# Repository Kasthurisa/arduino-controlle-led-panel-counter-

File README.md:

# arduino-controlle-led-panel-counter-
this project explains how to build arduino controlled led panel counter.  you have to use 16*32 led panel and arduino. here i just used atmega 328p microcontroler.

here is the pin connection for led pannel 

 nOE(D9) |1     2| A(D6)
 Gnd     |3     4| B(D7)
 Gnd     |5     6| C
 Gnd     |6     8| CLK(D13)
 Gnd     |7    10| SCLK(D8)
 Gnd     |11   12| R(D11)
 Gnd     |13   14| G
 Gnd     |15   16| D

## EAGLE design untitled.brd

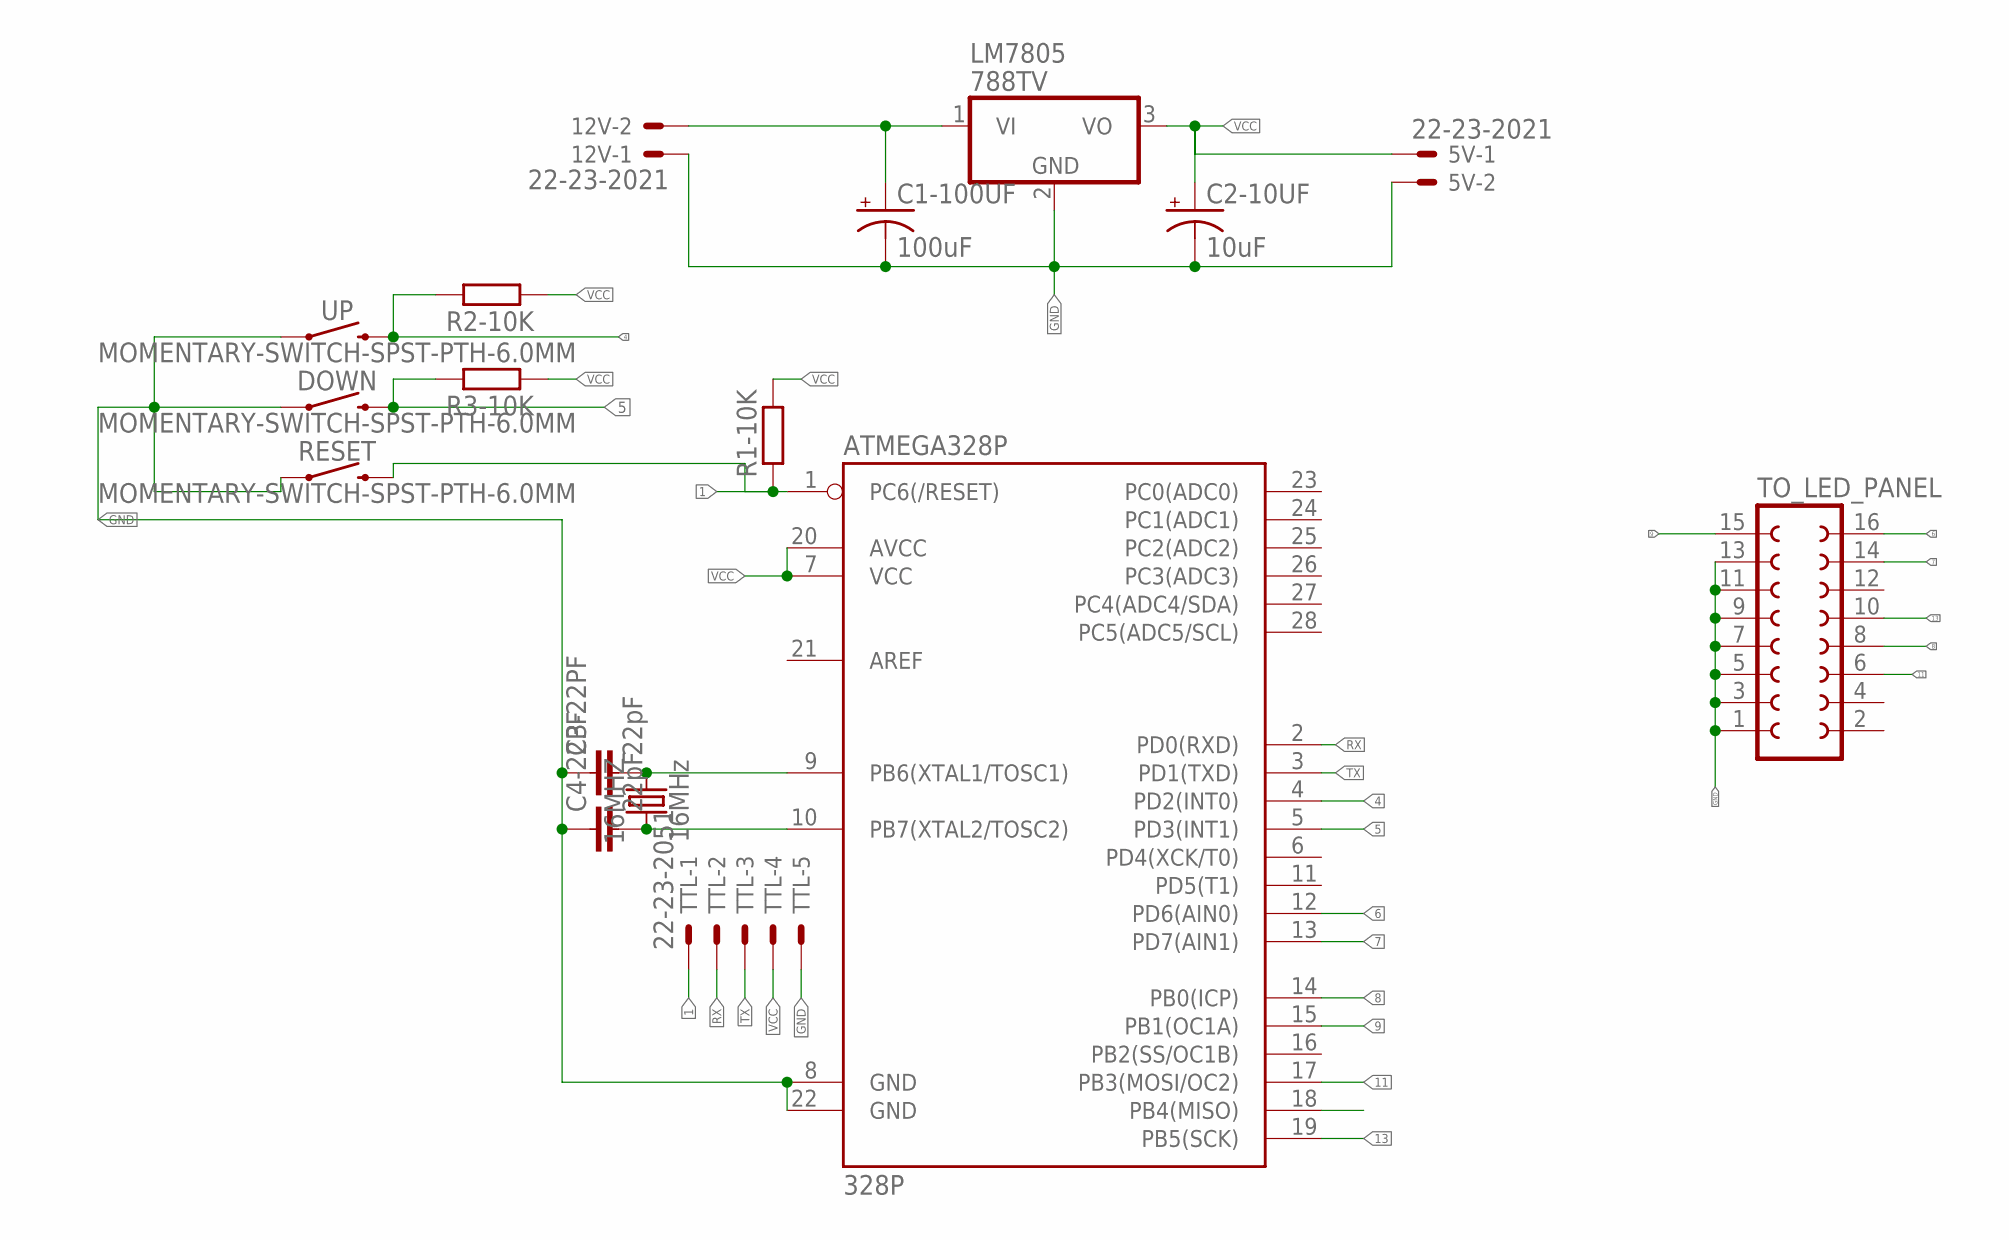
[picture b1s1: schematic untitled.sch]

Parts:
5V, 12V: 22-23-2021
16MHZ: 16MHz; HC49US
ATMEGA328P: 328P; DIP28
C1-100UF: 100uF; CPOL-RADIAL-2.5MM-6.5MM
C2-10UF: 10uF; CPOL-RADIAL-2.5MM-5MM
C3-22PF, C4-22PF: 22pF; CAP-PTH-2.54
DOWN: MOMENTARY-SWITCH-SPST-PTH-6.0MM; TACTILE_SWITCH_PTH_6.0MM
LM7805: 788TV; TO220V
R1-10K, R2-10K, R3-10K: R-EU_0207/10; 0207/10
RESET: MOMENTARY-SWITCH-SPST-PTH-6.0MM; TACTILE_SWITCH_PTH_6.0MM
TO_LED_PANEL: FE08-2
TTL: 22-23-2051
UP: MOMENTARY-SWITCH-SPST-PTH-6.0MM; TACTILE_SWITCH_PTH_6.0MM

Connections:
1: ATMEGA328P.1 (PC6(/RESET)), R1-10K.1, RESET.3 (2), TTL.1
4: ATMEGA328P.4 (PD2(INT0)), R2-10K.2, UP.3 (2)
5: ATMEGA328P.5 (PD3(INT1)), DOWN.3 (2), R3-10K.2
6: ATMEGA328P.12 (PD6(AIN0)), TO_LED_PANEL.16
7: ATMEGA328P.13 (PD7(AIN1)), TO_LED_PANEL.14
8: ATMEGA328P.14 (PB0(ICP)), TO_LED_PANEL.8
9: ATMEGA328P.15 (PB1(OC1A)), TO_LED_PANEL.15
11: ATMEGA328P.17 (PB3(MOSI/OC2)), TO_LED_PANEL.6
13: ATMEGA328P.19 (PB5(SCK)), TO_LED_PANEL.10
GND: 5V.2, 12V.1, ATMEGA328P.8 (GND), ATMEGA328P.22 (GND), C1-100UF.2 (-), C2-10UF.2 (-), C3-22PF.1, C4-22PF.1, DOWN.1, LM7805.2 (GND), RESET.1, TO_LED_PANEL.1, TO_LED_PANEL.3, TO_LED_PANEL.5, TO_LED_PANEL.7, TO_LED_PANEL.9, TO_LED_PANEL.11, TO_LED_PANEL.13, TTL.5, UP.1
unnamed: 16MHZ.2, ATMEGA328P.9 (PB6(XTAL1/TOSC1)), C3-22PF.2
unnamed: 16MHZ.1, ATMEGA328P.10 (PB7(XTAL2/TOSC2)), C4-22PF.2
RX: ATMEGA328P.2 (PD0(RXD)), TTL.2
TX: ATMEGA328P.3 (PD1(TXD)), TTL.3
VCC: 5V.1, ATMEGA328P.7 (VCC), ATMEGA328P.20 (AVCC), C2-10UF.1 (+), LM7805.3 (VO), R1-10K.2, R2-10K.1, R3-10K.1, TTL.4
VIN: 12V.2, C1-100UF.1 (+), LM7805.1 (VI)

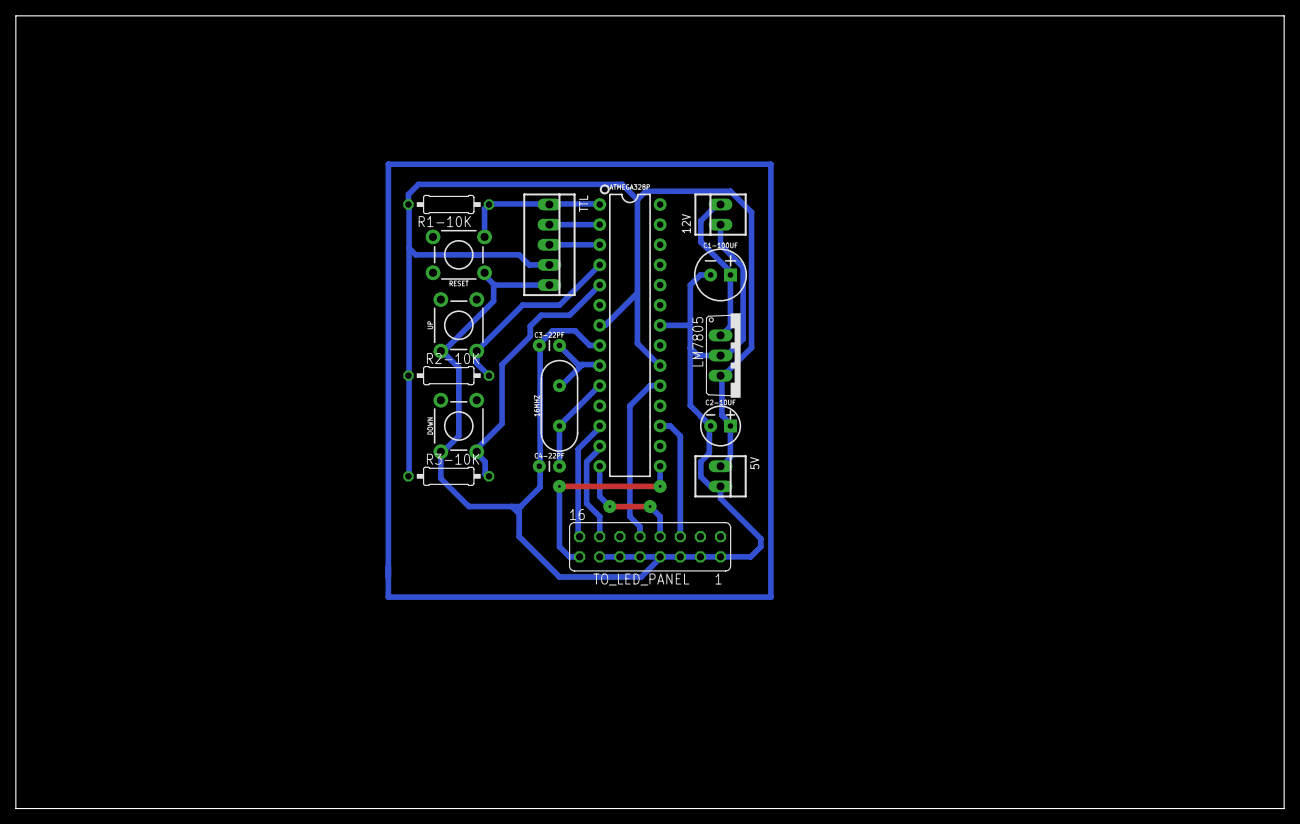
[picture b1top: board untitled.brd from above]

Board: 2 copper layers, 160.0 x 100.0 mm, 17 parts (0 on the bottom side), 16 nets.

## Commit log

2018-05-05 here i have added arduino code and eagle cad files for this project

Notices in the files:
parts and their libraries:
SparkFun-IC-Microcontroller: Licensing: Creative Commons ShareAlike 4.0 International - https://creativecommons.org/licenses/by-sa/4.0
